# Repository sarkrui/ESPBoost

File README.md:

# ESPBoost

### Introduction
The ESPBoost is an ESP32 shield combines a **MPU6050** (3-axis gyro/accelerometer, via **SDA/SCL** GPIO), 2 H-Bridge motor drivers (**L9110s**, via GPIO **5**, **16**,**17**,**18** ), and a DC-DC (4.5V ~17v to 5V) power regulator (for powering up the ESP board via USB, allowing to charge Li-Po and the ESP32 MCU). Attaching this shield onto a Lolin32, actuations that demand high current (max. 800mA for each bridge), for example, driving two DC motors, and detections of angles, acceleration can be easily made possible. 

### Components

* **Dual L9110s** (800 mA) DACs
* **MPU6050** Accelerometer and Gyroscope
* **TPS563201** Voltage regulator (4.5v to 17v input, 3A output)
* **FSR** (force sensitive resistor) connector  (A2 section)

### To-do

- [ ]  Include support for ESP32 minikit 
- [ ]  Incoporate [daisy chain support](https://i.imgur.com/pLPUlMk.jpg) for ESP boards (e.g. [TTGO T-Base](https://www.aliexpress.com/item/32888680096.html)) that come with an i2c connector (consisting of`SDA/SCL/3.3/GND` )
- [ ]  Add **ESPBoost-Input**, configured with 3-axis gyro/accelerometer (MPU6050), 12-pin capacitive sensor (MPR121q), FSR pull-down resistors
- [ ]  Add **ESPBoost-Actuation**, consisting of 2 sets of `TB6612FNG`
- [ ]  Add **ESPBoost-Power**, supporting battery charging, regulating voltage from 3.7V to 5V, 9V, 12V

### Pinout 

### Sample 
If you're interested in the field of Internet of Tangible Things, this shield may help. For sample inquiry, please drop me an email hi@pxing.design

### BibTex

```
@inproceedings{DBLP:conf/ewsn/XingC21,
  author    = {Sark Xing and
               Yaliang Chuang},
  title     = {ESPBoost: {A} Rapid Prototyping Toolkit for Helping Designers Create
               the Internet of Tangible Things},
  booktitle = {CHIIoT@EWSN/EICS},
  series    = {{CEUR} Workshop Proceedings},
  volume    = {2996},
  publisher = {CEUR-WS.org},
  year      = {2021}
}
```

### License

MIT License

Copyright (c) 2020 Sark Xing

Permission is hereby granted, free of charge, to any person obtaining a copy
of this software and associated documentation files (the "Software"), to deal
in the Software without restriction, including without limitation the rights
to use, copy, modify, merge, publish, distribute, sublicense, and/or sell
copies of the Software, and to permit persons to whom the Software is
furnished to do so, subject to the following conditions:

The above copyright notice and this permission notice shall be included in all
copies or substantial portions of the Software.

THE SOFTWARE IS PROVIDED "AS IS", WITHOUT WARRANTY OF ANY KIND, EXPRESS OR
IMPLIED, INCLUDING BUT NOT LIMITED TO THE WARRANTIES OF MERCHANTABILITY,
FITNESS FOR A PARTICULAR PURPOSE AND NONINFRINGEMENT. IN NO EVENT SHALL THE
AUTHORS OR COPYRIGHT HOLDERS BE LIABLE FOR ANY CLAIM, DAMAGES OR OTHER
LIABILITY, WHETHER IN AN ACTION OF CONTRACT, TORT OR OTHERWISE, ARISING FROM,
OUT OF OR IN CONNECTION WITH THE SOFTWARE OR THE USE OR OTHER DEALINGS IN THE
SOFTWARE.

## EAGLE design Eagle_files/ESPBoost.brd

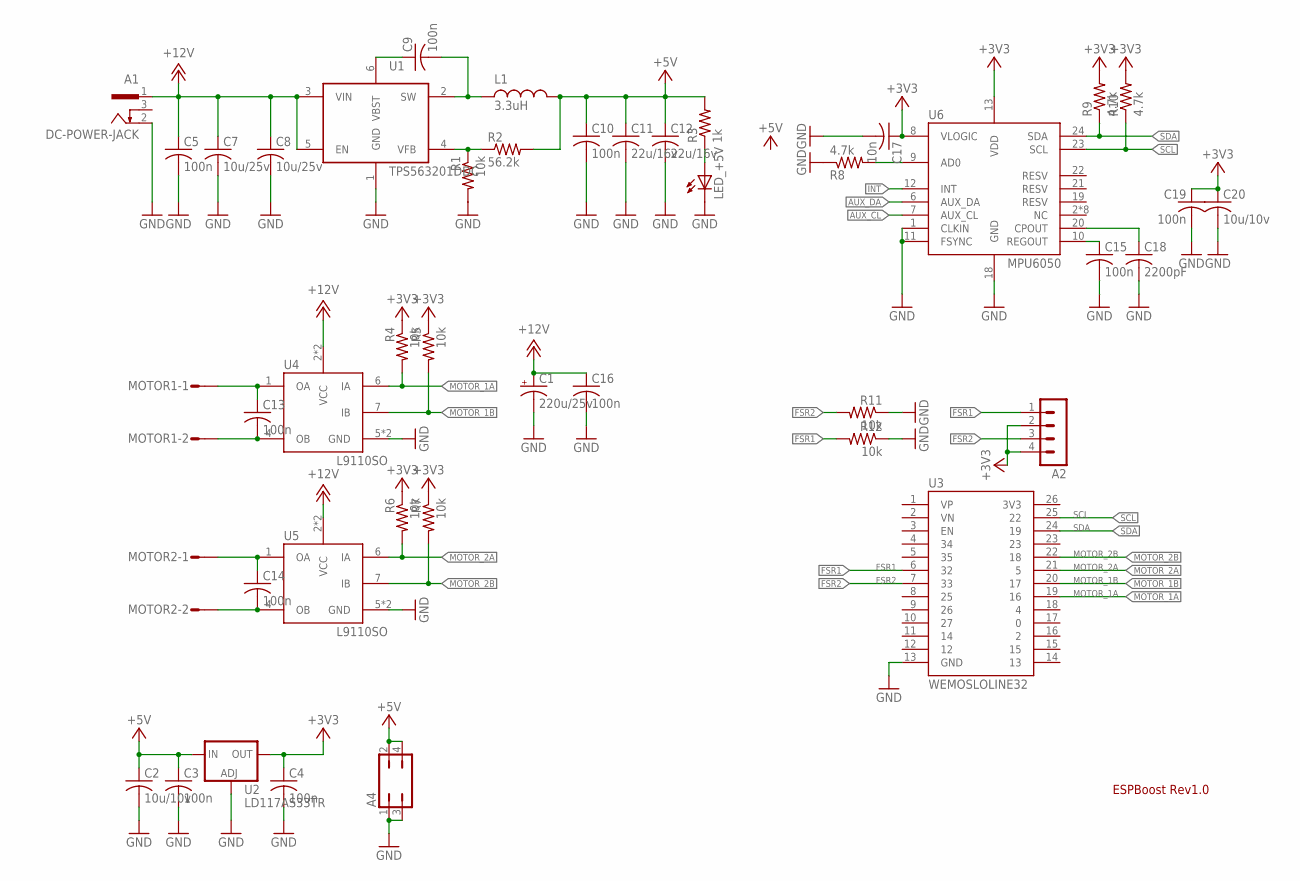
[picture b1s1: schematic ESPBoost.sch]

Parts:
A1: DC-POWER-JACK; DC-POWER
A2: MA04-1
A4: JP2Q
C1: 220u/25v; E3,5-8
C2, C20: 10u/10v; C0805
C3, C4, C5, C9, C10, C13, C14, C15, C16, C19: 100n; C0805
C7, C8: 10u/25v; C1206
C11, C12: 22u/16v; C1206
C17: 10n; C0805
C18: 2200pF; C0805
L1: 3.3uH; SLF7032TYPE
LED_+5V: LEDCHIPLED_0805; CHIPLED_0805
MOTOR1, MOTOR2: S02P
R1, R4, R5, R6, R7, R11, R12: 10k; R0805
R2: 56.2k; R0805
R3: 1k; R0805
R8, R9, R10: 4.7k; R0805
U1: TPS563201DDC; SOT23-6L
U2: LD117AS33TR; SOT223
U3: WEMOSLOLINE32; WEMOSLOLIN32
U4, U5: L9110SO; SO08
U6: MPU6050; QFN24

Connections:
+3V3: A2.2, A2.4, C4.1, C17.1, C19.1, C20.1, R4.1, R5.1, R6.1, R7.1, R9.2, R10.2, U2.4 (OUT), U6.8 (VLOGIC), U6.13 (VDD)
+5V: A4.2, A4.4, C2.1, C3.1, C10.1, C11.1, C12.1, L1.2, R2.2, R3.2, U2.3 (IN)
+12V: A1.1, C1.+, C5.1, C7.1, C8.1, C16.1, U1.3 (VIN), U1.5 (EN), U4.2 (VCC), U4.3 (VCC), U5.2 (VCC), U5.3 (VCC)
AUX_CL: U6.7 (AUX_CL)
AUX_DA: U6.6 (AUX_DA)
FSR1: A2.1, R12.2, U3.6 (32)
FSR2: A2.3, R11.2, U3.7 (33)
GND: A1.2, A4.1, A4.3, C1.-, C2.2, C3.2, C4.2, C5.2, C7.2, C8.2, C10.2, C11.2, C12.2, C15.2, C16.2, C17.2, C18.2, C19.2, C20.2, LED_+5V.C, R1.2, R8.1, R11.1, R12.1, U1.1 (GND), U2.1 (ADJ), U3.13 (GND), U4.5 (GND), U4.8 (GND), U5.5 (GND), U5.8 (GND), U6.1 (CLKIN), U6.11 (FSYNC), U6.18 (GND)
INT: U6.12 (INT)
MOTOR_1A: R4.2, U3.19 (16), U4.6 (IA)
MOTOR_1B: R5.2, U3.20 (17), U4.7 (IB)
MOTOR_1OA: C13.1, MOTOR1.1, U4.1 (OA)
MOTOR_1OB: C13.2, MOTOR1.2, U4.4 (OB)
MOTOR_2A: R6.2, U3.21 (5), U5.6 (IA)
MOTOR_2B: R7.2, U3.22 (18), U5.7 (IB)
MOTOR_2OA: C14.1, MOTOR2.1, U5.1 (OA)
MOTOR_2OB: C14.2, MOTOR2.2, U5.4 (OB)
unnamed: LED_+5V.A, R3.1
unnamed: C9.2, L1.1, U1.2 (SW)
unnamed: R1.1, R2.1, U1.4 (VFB)
unnamed: C9.1, U1.6 (VBST)
unnamed: R8.2, U6.9 (AD0)
unnamed: C15.1, U6.10 (REGOUT)
unnamed: C18.1, U6.20 (CPOUT)
SCL: R10.1, U3.25 (22), U6.23 (SCL)
SDA: R9.1, U3.24 (19), U6.24 (SDA)

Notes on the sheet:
ESPBoost Rev1.0

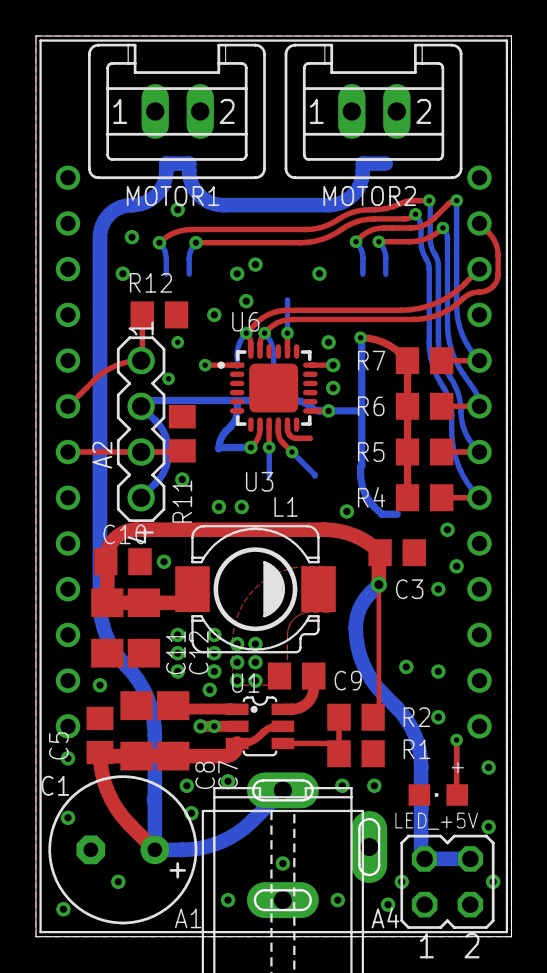
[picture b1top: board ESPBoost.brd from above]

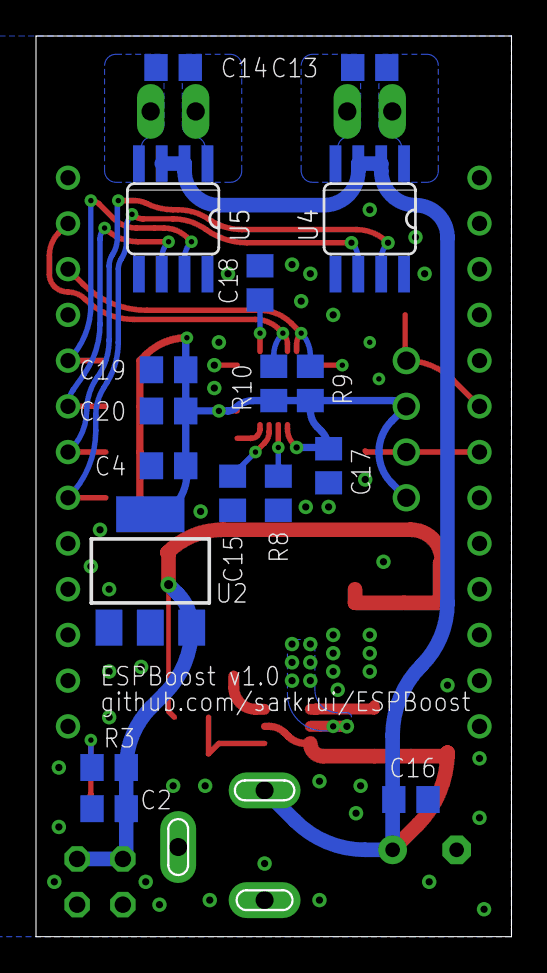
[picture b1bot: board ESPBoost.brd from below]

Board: 2 copper layers, 26.3 x 49.9 mm, 44 parts (17 on the bottom side), 23 nets.

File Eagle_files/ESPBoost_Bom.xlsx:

| Project | ESPBoost | Board Serial: | ESPBoost Rev1.0
# | Name | Value | Package | Mark | Amount
1 | SMD Ceramics Capacitor | 100n/25v | 0805 | C3, C4, C5, C9, C10, C13, C14, C15, C16, C19 | 10
2 | SMD Ceramics Capacitor | 10n/25v | 0806 | C17 | 1
3 | SMD Ceramics Capacitor | 10u/10v | 0807 | C2, C20 | 2
4 | SMD Ceramics Capacitor | 10u/25v | 1206 | C7, C8 | 2
5 | SMD Ceramics Capacitor | 2200pF | 0805 | C18 | 1
6 | Electrolytic capacitor | 220u/25v | ø8, d3.5mm | C1 | 1
7 | SMD Ceramics Capacitor | 22u/16v | 1206 | C11, C12 | 2
8 | SMD Inductance | 3.3uH/3A | SLF7032 | L1 | 1
9 | SMD Resistor | 4.7k | 0805 | R8, R9, R10 | 3
10 | SMD Resistor | 10k | 0805 | R1, R4, R5, R6, R7, R11, R12 | 7
11 | SMD Resistor | 1k | 0805 | R3 | 1
12 | SMD Resistor | 56.2k | 0805 | R2 | 1
13 | SMD LED | Red | 0805 | LED_+5V | 1
14 | Power Jack | DC-POWER-JACK | In-line | A1 | 1
15 | Motor Driver | L9110SO | SO08 | U4, U5 | 2
16 | Linear Regulator | LD117AS33TR | SOT223 | U2 | 1
17 | Accelerometer and Gyroscope | MPU6050 | QFN24 | U6 | 1
18 | DCDC | TPS563201DDC | SOT23-6L | U1 | 1
19 | ESP Pin | female | d2.54, 13 pins | U3 | 2
20 | Single-row pin header | male | d2.54, 4 pins | A4 | 1
21 | Double-row pin header | male | d2.54, 5 pins | A2 | 1
22 | JST2.0 | male | d2.54, 2 pins | MOTOR1, MOTOR2 | 2

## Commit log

2020-05-14 ESPBoost v1.0 inital release (PCB, Schematics, BOM)
2020-05-14 add board annotation
2020-06-04 add pinout vector
2020-08-25 Set theme jekyll-theme-minimal
2022-01-07 add BibTex
